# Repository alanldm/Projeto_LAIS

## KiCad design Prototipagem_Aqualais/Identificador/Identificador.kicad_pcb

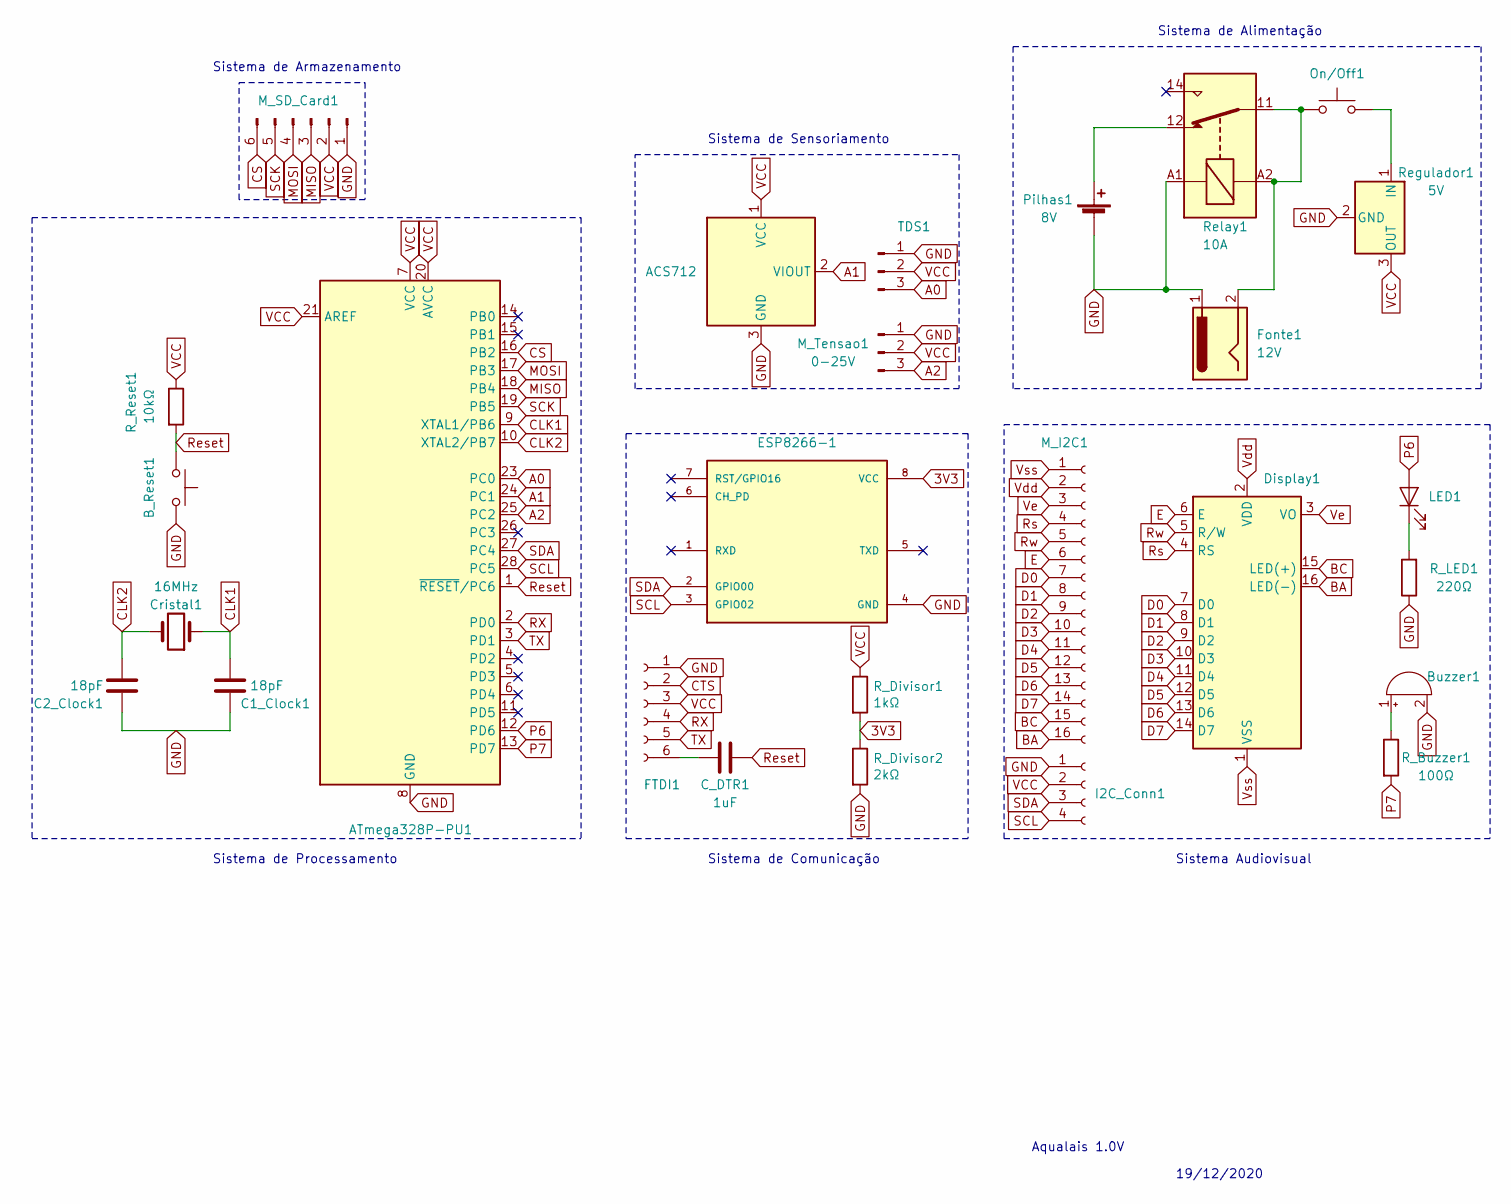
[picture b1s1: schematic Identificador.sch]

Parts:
ACS712: PinHeader_1x03_P2.54mm_Vertical
ATmega328P-PU1: DIP-28_W7.62mm
B_Reset1: SW_PUSH_6mm
Buzzer1: MagneticBuzzer_ProSignal_ABT-410-RC
C1_Clock1, C2_Clock1: 18pF; C_Disc_D7.5mm_W5.0mm_P5.00mm
C_DTR1: 1uF; C_Radial_D5.0mm_H7.0mm_P2.00mm
Cristal1: 16MHz; Crystal_HC49-4H_Vertical
Display1: WC1602A
ESP8266-1: ESP-01
FTDI1: PinSocket_1x06_P2.54mm_Horizontal
Fonte1: 12V; BarrelJack_CUI_PJ-063AH_Horizontal
I2C_Conn1: PinHeader_1x04_P2.54mm_Vertical
LED1: LED_D5.0mm_Horizontal_O6.35mm_Z3.0mm
M_I2C1: PinHeader_1x16_P2.54mm_Vertical
M_SD_Card1: (no value)
M_Tensao1: 0-25V; PinHeader_1x03_P2.54mm_Vertical
On/Off1: SolderWirePad_1x02_P7.62mm_Drill2mm
Pilhas1: 8V; BatteryHolder_Keystone_2468_2xAAA
R_Buzzer1: 100Ω; R_Axial_DIN0309_L9.0mm_D3.2mm_P12.70mm_Horizontal
R_Divisor1: 1kΩ; R_Axial_DIN0309_L9.0mm_D3.2mm_P12.70mm_Horizontal
R_Divisor2: 2kΩ; R_Axial_DIN0309_L9.0mm_D3.2mm_P12.70mm_Horizontal
R_LED1: 220Ω; R_Axial_DIN0309_L9.0mm_D3.2mm_P12.70mm_Horizontal
R_Reset1: 10kΩ; R_Axial_DIN0309_L9.0mm_D3.2mm_P12.70mm_Horizontal
Regulador1: 5V; PinHeader_1x03_P2.54mm_Vertical
Relay1: 10A; Relay_1-Form-C_Schrack-RYII_RM3.2mm
TDS1: PinHeader_1x03_P2.54mm_Vertical

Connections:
3V3: ESP8266-1.8 (VCC), R_Divisor1.2, R_Divisor2.1
A0: ATmega328P-PU1.23 (PC0), TDS1.3
A1: ACS712.2 (VIOUT), ATmega328P-PU1.24 (PC1)
A2: ATmega328P-PU1.25 (PC2), M_Tensao1.3; also elsewhere on the board
BA: Display1.16 (LED(-)), M_I2C1.16
BC: Display1.15 (LED(+)), M_I2C1.15
CLK1: ATmega328P-PU1.9 (XTAL1/PB6), C1_Clock1.2, Cristal1.1
CLK2: ATmega328P-PU1.10 (XTAL2/PB7), C2_Clock1.2, Cristal1.2
CS: ATmega328P-PU1.16 (PB2), M_SD_Card1.6; also elsewhere on the board
CTS: FTDI1.2
D0: Display1.7 (D0), M_I2C1.7
D1: Display1.8 (D1), M_I2C1.8
D2: Display1.9 (D2), M_I2C1.9
D3: Display1.10 (D3), M_I2C1.10
D4: Display1.11 (D4), M_I2C1.11
D5: Display1.12 (D5), M_I2C1.12
D6: Display1.13 (D6), M_I2C1.13
D7: Display1.14 (D7), M_I2C1.14
E: Display1.6 (E), M_I2C1.6
GND: ACS712.3 (GND), ATmega328P-PU1.8 (GND), ATmega328P-PU1.22 (GND), B_Reset1.2, Buzzer1.2 (+), C1_Clock1.1, C2_Clock1.1, ESP8266-1.4 (GND), FTDI1.1, Fonte1.1, I2C_Conn1.1, M_SD_Card1.1, M_Tensao1.1, Pilhas1.2 (-), R_Divisor2.2, R_LED1.1, Regulador1.2 (GND), Relay1.A1, TDS1.1; also elsewhere on the board
MISO: ATmega328P-PU1.18 (PB4), M_SD_Card1.3; also elsewhere on the board
MOSI: ATmega328P-PU1.17 (PB3), M_SD_Card1.4; also elsewhere on the board
unnamed: Buzzer1.1 (-), R_Buzzer1.1
unnamed: C_DTR1.1, FTDI1.6
unnamed: Fonte1.2, On/Off1.1, Relay1.11, Relay1.A2
unnamed: LED1.1 (K), R_LED1.2
unnamed: On/Off1.2, Regulador1.1 (IN)
unnamed: Pilhas1.1 (+), Relay1.12
P6: ATmega328P-PU1.12 (PD6), LED1.2 (A)
P7: ATmega328P-PU1.13 (PD7), R_Buzzer1.2
RX: ATmega328P-PU1.2 (PD0), FTDI1.4
Reset: ATmega328P-PU1.1 (~RESET~/PC6), B_Reset1.1, C_DTR1.2, R_Reset1.2
Rs: Display1.4 (RS), M_I2C1.4
Rw: Display1.5 (R/W), M_I2C1.5
SCK: ATmega328P-PU1.19 (PB5), M_SD_Card1.5; also elsewhere on the board
SCL: ATmega328P-PU1.28 (PC5), ESP8266-1.3 (GPIO02), I2C_Conn1.4
SDA: ATmega328P-PU1.27 (PC4), ESP8266-1.2 (GPIO00), I2C_Conn1.3
TX: ATmega328P-PU1.3 (PD1), FTDI1.5
VCC: ACS712.1 (VCC), ATmega328P-PU1.7 (VCC), ATmega328P-PU1.20 (AVCC), ATmega328P-PU1.21 (AREF), FTDI1.3, I2C_Conn1.2, M_SD_Card1.2, M_Tensao1.2, R_Divisor1.1, R_Reset1.1, Regulador1.3 (OUT), TDS1.2; also elsewhere on the board
Vdd: Display1.2 (VDD), M_I2C1.2
Ve: Display1.3 (VO), M_I2C1.3
Vss: Display1.1 (VSS), M_I2C1.1

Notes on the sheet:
Sistema de Alimentação
Sistema Audiovisual
Sistema de Armazenamento
Sistema de Comunicação
Sistema de Sensoriamento
Sistema de Processamento
19/12/2020
Aqualais 1.0V

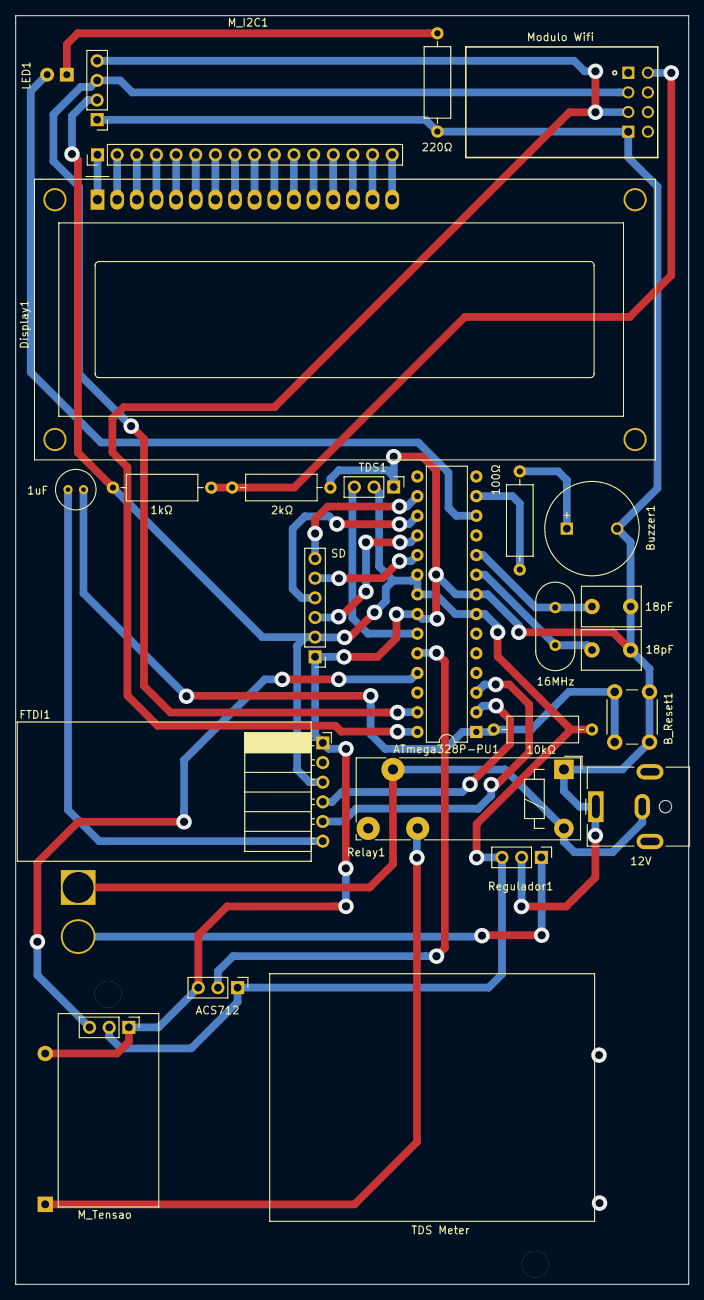
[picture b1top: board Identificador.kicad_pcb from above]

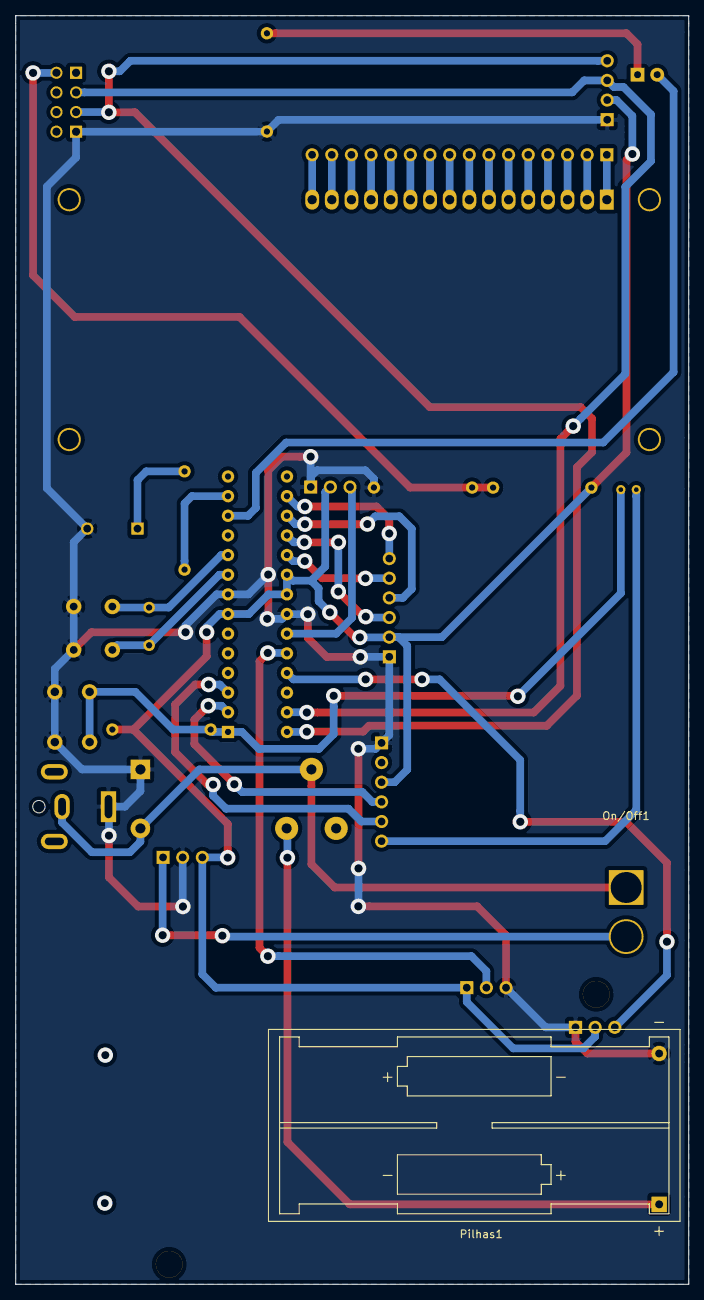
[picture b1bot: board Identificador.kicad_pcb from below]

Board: 2 copper layers, 87.0 x 164.0 mm, 27 parts (2 on the bottom side), 41 nets.

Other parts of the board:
 : M_Tensao; PinHeader_1x03_P2.54mm_Vertical
SD: PinHeader_1x06_P2.54mm_Vertical

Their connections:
A2: .3; also elsewhere on the board
CS: SD.6; also elsewhere on the board
GND: .1, SD.1; also elsewhere on the board
MISO: SD.3; also elsewhere on the board
MOSI: SD.4; also elsewhere on the board
SCK: SD.5; also elsewhere on the board
VCC: .2, SD.2; also elsewhere on the board
